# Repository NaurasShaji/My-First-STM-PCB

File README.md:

# My First PCB - Microcontroller and USB Interface Board

## 📋 Project Overview

This repository contains the design files for my first printed circuit board (PCB) - a microcontroller and USB interface system built around the STM32F103C8T6 ARM Cortex-M3 processor. This project represents a significant milestone in my electronics engineering journey, demonstrating practical application of hardware design principles.

## 🔧 Hardware Specifications

### Core Components
- **Microcontroller**: STM32F103C8T6 (ARM Cortex-M3, 72MHz, 64KB Flash, 20KB RAM)
- **Power Management**: AMS1117-3.3V Linear Voltage Regulator
- **Connectivity**: USB-C Connector for data and power
- **Clock Source**: 16MHz Crystal Oscillator
- **Voltage Rails**: 5V and 3.3V power distribution

### Key Features
- ✅ Complete GPIO breakout for all microcontroller pins
- ✅ USB-C interface with proper differential pair routing
- ✅ Comprehensive power decoupling network
- ✅ External crystal oscillator for precise timing
- ✅ Power LED indicators
- ✅ Reset button for system control

## 📁 Repository Structure

```
├── Hardware/
│   ├── Schematics/
│   │   └── pcb-schematic.pdf
│   ├── PCB_Layout/
│   │   └── pcb-layout.pdf
│   ├── Gerber_Files/
│   │   └── manufacturing_files/
│   └── BOM/
│       └── bill_of_materials.xlsx
├── Documentation/
│   ├── Design_Notes.md
│   └── Pin_Mapping.md
├── Images/
│   ├── pcb_3d_render.png
│   └── schematic_overview.png
└── README.md
```

## 🛠️ Design Tools

- **EDA Software**: KiCad 7.x
- **Schematic Capture**: KiCad Eeschema
- **PCB Layout**: KiCad Pcbnew
- **3D Visualization**: KiCad 3D Viewer

## ⚡ Power Architecture

### Power Supply Design
- **Input**: 5V via USB-C or external power jack
- **Regulation**: AMS1117-3.3V for stable 3.3V rail
- **Decoupling**: Multiple capacitor values (1µF, 100nF, 10nF) for clean power delivery
- **Protection**: Reverse polarity protection and overcurrent limiting

### Power Consumption
- **Active Mode**: ~20mA (estimated)
- **Sleep Mode**: <1mA (microcontroller dependent)

## 🔌 Pinout and Connectivity

### USB-C Interface
- **Power**: VBUS, GND
- **Data**: D+, D- (USB 2.0 Full Speed)
- **Configuration**: CC1, CC2 for USB-C compliance

### GPIO Breakout
- All STM32F103C8T6 pins accessible via 0.1" headers
- Standard pin numbering and labeling
- Compatible with breadboard prototyping

## 📐 PCB Specifications

- **Board Size**: 50mm x 30mm (approximate)
- **Layer Count**: 2-layer PCB
- **Thickness**: 1.6mm standard
- **Copper Weight**: 1oz
- **Via Size**: 0.2mm drill, 0.45mm pad
- **Minimum Trace Width**: 0.15mm
- **Minimum Spacing**: 0.15mm

## 🔧 Manufacturing Notes

### PCB Fabrication
- Standard FR4 substrate
- HASL (Hot Air Solder Leveling) finish
- Green solder mask with white silkscreen
- Design Rule Check (DRC) compliant

### Assembly Considerations
- SMD components: 0805 and SOIC packages
- Through-hole components for headers and connectors
- Hand soldering friendly component selection

## 📊 Bill of Materials (BOM)

| Designator | Component | Package | Quantity | Notes |
|------------|-----------|---------|----------|-------|
| U1 | STM32F103C8T6 | LQFP-48 | 1 | Main microcontroller |
| U2 | AMS1117-3.3 | SOT-223 | 1 | Voltage regulator |
| J1 | USB-C Connector | USB-C | 1 | Power and data |
| Y1 | 16MHz Crystal | HC-49S | 1 | Clock source |
| C1-C10 | Various Capacitors | 0805 | 10 | Decoupling and filtering |
| R1-R5 | Various Resistors | 0805 | 5 | Pull-ups and current limiting |

*Complete BOM available in `/Hardware/BOM/` directory*

## 🚀 Getting Started

### Prerequisites
- KiCad 7.x or later
- Basic understanding of PCB design principles
- PCB manufacturing service account (JLCPCB, PCBWay, etc.)

### Viewing the Design
1. Clone this repository
2. Open the `.kicad_pro` file in KiCad
3. View schematics in Eeschema
4. Examine PCB layout in Pcbnew

### Manufacturing
1. Generate Gerber files from Pcbnew
2. Create drill files
3. Export pick and place files (if needed)
4. Upload to your preferred PCB manufacturer

## 📈 Future Improvements

- [ ] Add USB bootloader capability
- [ ] Implement USB device classes (CDC, HID)
- [ ] Add onboard sensors (temperature, accelerometer)
- [ ] Improve power efficiency with switching regulator
- [ ] Add wireless connectivity (ESP32 integration)
- [ ] Implement proper EMI/EMC design practices

## 🤝 Contributing

This is a learning project, but suggestions and improvements are welcome! Please feel free to:
- Open issues for design discussions
- Submit pull requests for documentation improvements
- Share your own implementations and modifications

## 📄 License

This project is open source and available under the [MIT License](LICENSE).

## 👨‍💻 Author

**[Your Name]**
- B.Tech ECE Final Year Student
- Electronics and Hardware Design Enthusiast
- GitHub:https://github.com/NaurasShaji
- LinkedIn:https://www.linkedin.com/in/nauras-shaji-/

## 🙏 Acknowledgments

- STMicroelectronics for comprehensive documentation
- KiCad development team for the excellent EDA tools
- Electronics engineering community for inspiration and guidance
- My professors and mentors for their support

***

⭐ **If you find this project helpful, please consider giving it a star!** ⭐

**Project Status**: ✅ Design Complete | 🔄 Testing Phase | 📋 Documentation In Progress

*Last Updated: September 10, 2025*

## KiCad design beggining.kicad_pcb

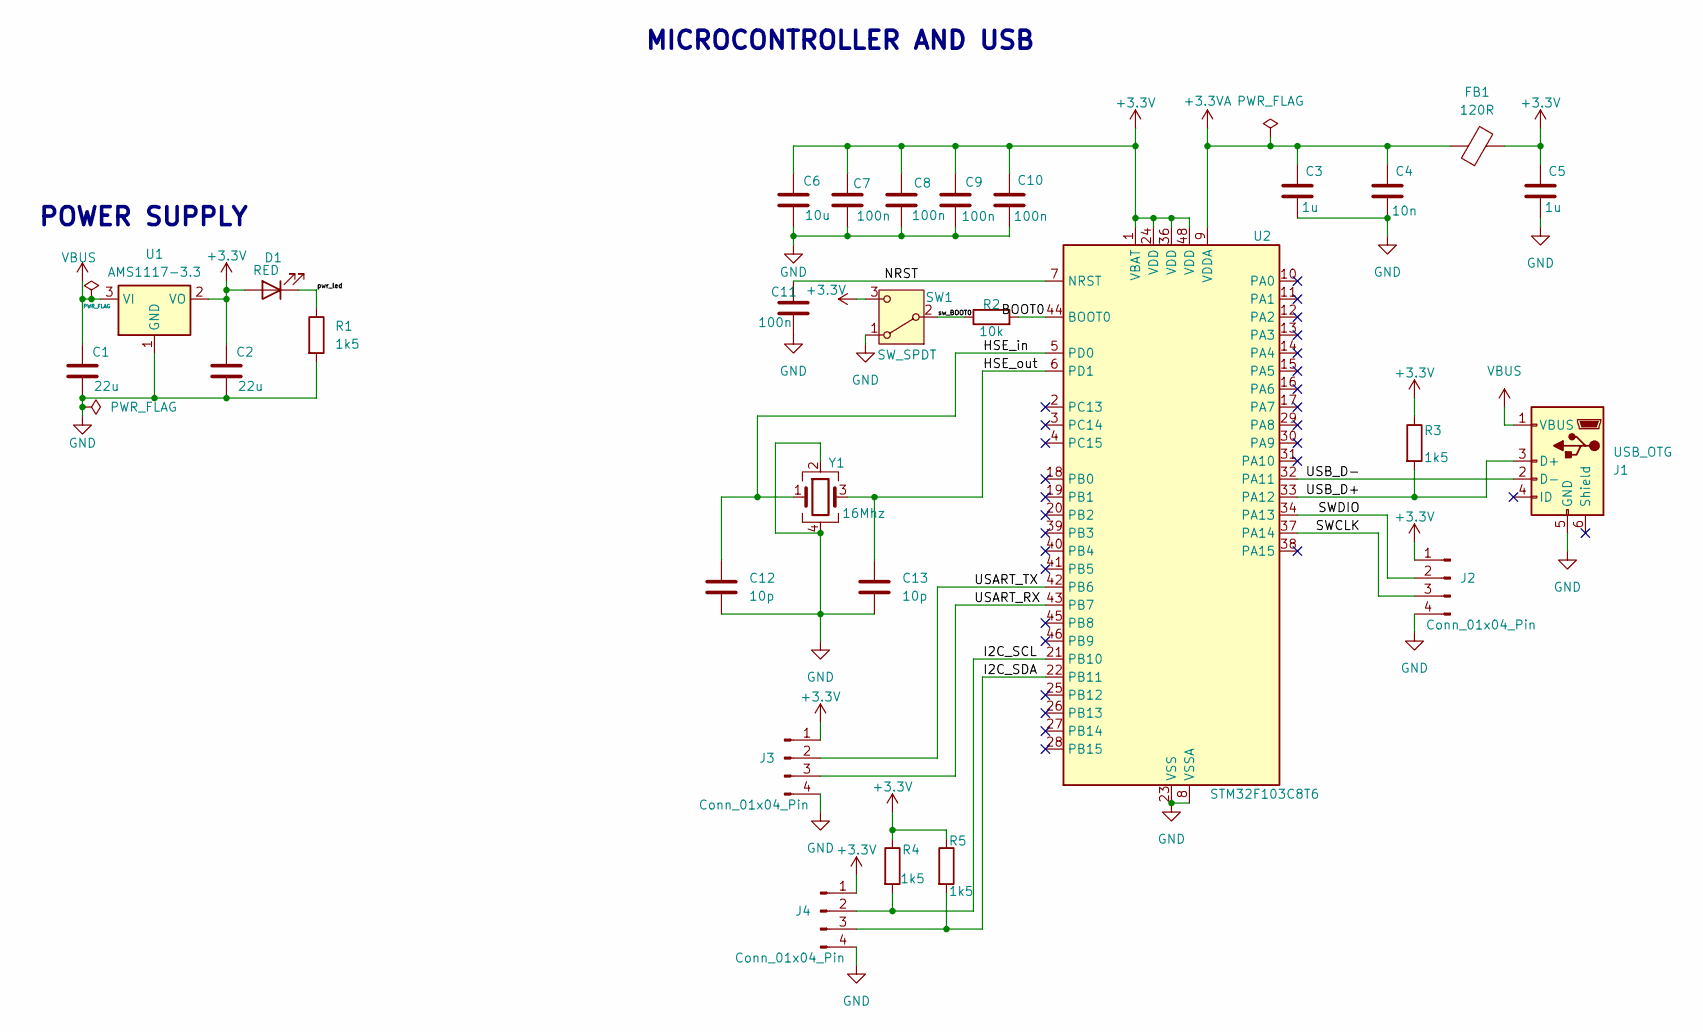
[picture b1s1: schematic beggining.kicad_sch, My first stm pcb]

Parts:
C1, C2: 22u; C_0805_2012Metric
C3, C5: 1u; C_0402_1005Metric
C4: 10n; C_0402_1005Metric
C6: 10u; C_0603_1608Metric
C7, C8, C9, C10, C11: 100n; C_0402_1005Metric
C12, C13: 10p; C_0402_1005Metric
D1: RED; LED_0603_1608Metric
FB1: 120R; L_0603_1608Metric
J1: USB_OTG; USB_Micro-B_Wuerth_614105150721_Vertical_CircularHoles
J2, J3, J4: Conn_01x04_Pin; PinHeader_1x04_P1.00mm_Vertical
R1, R3, R4, R5: 1k5; R_0402_1005Metric
R2: 10k; R_0402_1005Metric
SW1: SW_SPDT; SW_E-Switch_EG1224_SPDT_Angled
U1: AMS1117-3.3; SOT-223-3_TabPin2
U2: STM32F103C8T6; LQFP-48_7x7mm_P0.5mm
Y1: 16Mhz; Crystal_SMD_3225-4Pin_3.2x2.5mm

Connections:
+3.3V: C2.1, C5.1, C6.1, C7.1, C8.1, C9.1, C10.1, D1.2 (A), FB1.2, J2.1, J3.1, J4.1, R3.1, R4.1, R5.1, SW1.3 (C), U1.2 (VO), U2.1 (VBAT), U2.24 (VDD), U2.36 (VDD), U2.48 (VDD)
+3.3VA: C3.1, C4.1, FB1.1, U2.9 (VDDA)
/BOOT0: R2.2, U2.44 (BOOT0)
/HSE_in: C12.1, U2.5 (PD0), Y1.1
/HSE_out: C13.1, U2.6 (PD1), Y1.3
/I2C_SCL: J4.2, R4.2, U2.21 (PB10)
/I2C_SDA: J4.3, R5.2, U2.22 (PB11)
/NRST: C11.1, U2.7 (NRST)
/SWCLK: J2.3, U2.37 (PA14)
/SWDIO: J2.2, U2.34 (PA13)
/USART_RX: J3.3, U2.43 (PB7)
/USART_TX: J3.2, U2.42 (PB6)
/USB_D+: J1.3 (D+), R3.2, U2.33 (PA12)
/USB_D-: J1.2 (D-), U2.32 (PA11)
/pwr_led: D1.1 (K), R1.1
/sw_BOOT0: R2.1, SW1.2 (B)
GND: C1.2, C2.2, C3.2, C4.2, C5.2, C6.2, C7.2, C8.2, C9.2, C10.2, C11.2, C12.2, C13.2, J1.5 (GND), J2.4, J3.4, J4.4, R1.2, SW1.1 (A), U1.1 (GND), U2.8 (VSSA), U2.23 (VSS), U2.35 (VSS), U2.47 (VSS), Y1.2, Y1.4
VBUS: C1.1, J1.1 (VBUS), U1.3 (VI)

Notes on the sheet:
POWER SUPPLY
MICROCONTROLLER AND USB

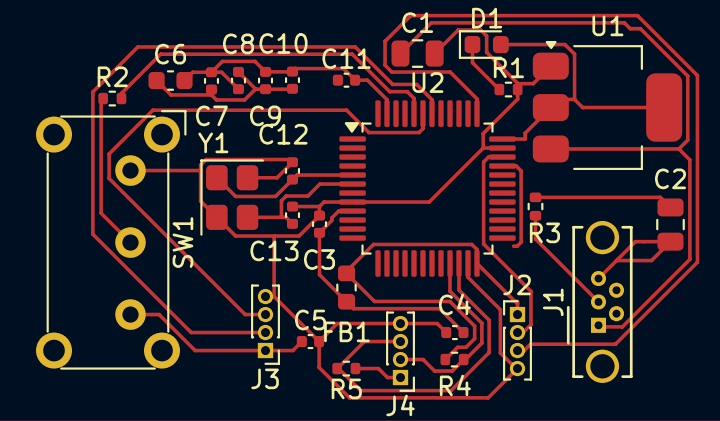
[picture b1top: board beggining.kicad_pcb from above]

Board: 2 copper layers, 28 parts (0 on the bottom side), 18 nets.

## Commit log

2025-09-10 Create README.md for PCB project documentation
    Added comprehensive README for PCB project detailing specifications, design tools, and usage instructions.
2025-09-10 Fix GitHub and LinkedIn profile links
    Updated GitHub and LinkedIn links for clarity.
